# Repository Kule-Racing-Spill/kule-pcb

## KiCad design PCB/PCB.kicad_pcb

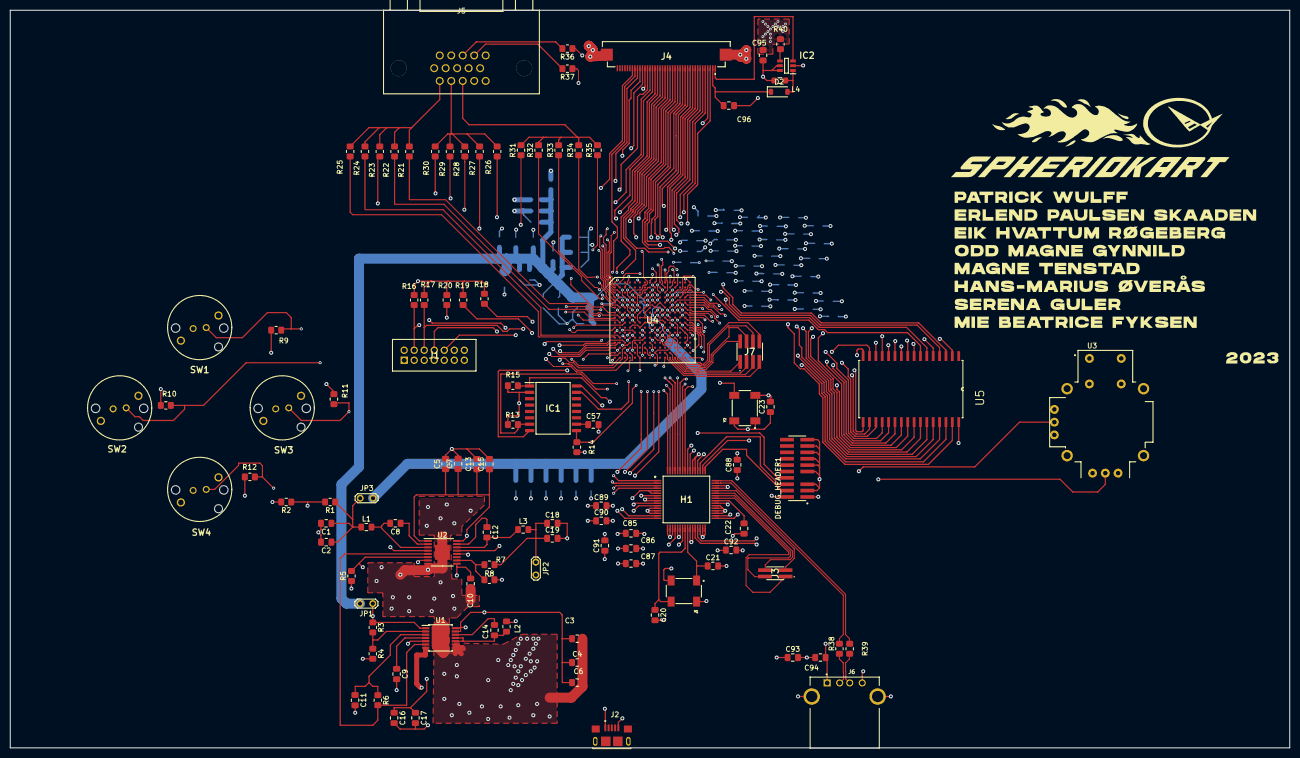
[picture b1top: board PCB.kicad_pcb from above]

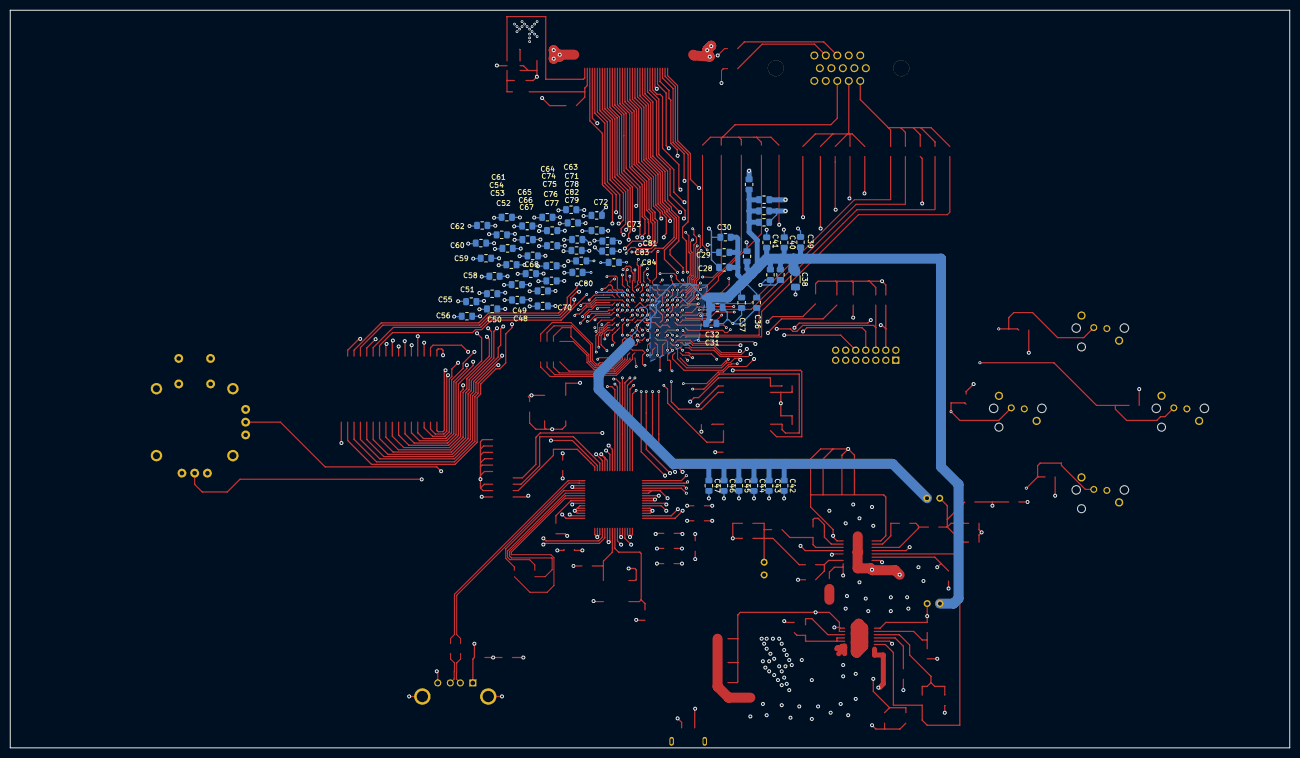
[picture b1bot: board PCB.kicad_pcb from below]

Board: 6 copper layers, 255.0 x 147.0 mm, 166 parts (60 on the bottom side), 163 nets.

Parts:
C1, C2, C16, C17, C18, C19: 22u; C_0805_2012Metric_Pad1.18x1.45mm_HandSolder
C3, C41, C94: 100u; C_0805_2012Metric_Pad1.18x1.45mm_HandSolder
C4, C5, C13, C92: 10u; C_0805_2012Metric_Pad1.18x1.45mm_HandSolder
C6, C7, C8, C12, C14, C15, C23, C57, C85, C86, C87, C88, C89, C90, C91: 100n; C_0805_2012Metric_Pad1.18x1.45mm_HandSolder
C9: 3.3n; C_0805_2012Metric_Pad1.18x1.45mm_HandSolder
C10, C11, C22, C93, C96: 1u; C_0805_2012Metric_Pad1.18x1.45mm_HandSolder
C20, C21: 12p; C_0805_2012Metric_Pad1.18x1.45mm_HandSolder
C24, C25, C26, C27, C28, C29, C30, C31, C39, C40, C42, C43, C44, C48, C49, C50, C51, C55, C56, C58, C59, C63, C64, C65, C66, C70, C71, C72, C73, C77, C78, C79, C80: 470n; C_0805_2012Metric_Pad1.18x1.45mm_HandSolder
C32, C33, C34, C35, C36, C37, C45, C46, C52, C53, C60, C61, C67, C68, C74, C75, C81, C82, C95: 4.7u; C_0805_2012Metric_Pad1.18x1.45mm_HandSolder
C38: 330u; C_1206_3216Metric_Pad1.33x1.80mm_HandSolder
C47, C54, C62, C69, C76, C83, C84: 47u; C_0805_2012Metric_Pad1.18x1.45mm_HandSolder
D2: MBR0520; D_SOD-123
DEBUG_HEADER1: FTSH-110-01-L-DV-007; SAMTEC_FTSH-110-01-L-DV-007
H1: EFM32GG332F1024-QFP64; QFP50P1200X1200X120-64N
IC1: S25FL256LAGMFI003; SOIC127P1030X265-16N
IC2: LT1932ES6#TRMPBF; SOT95P280X100-6N
J1: 0878311420
J2: USB_B_Micro; AMPHENOL_10118193-0001LF
J3: FTS-102-02-F-DV-TR; FTS-102-YY-XX-DV-TR
J4: 62684-402100ALF; 62684402100ALF
J5: L77HDE15SD1CH4FVGA; CONN_L77HDE15SD1CH4FVGA_AMP
J6: USB1130-15-A_REVA; GCT_USB1130-15-A_REVA
J7: FTSH-104-01-F-DV; FTSH-104-XX-YYY-DV
JP1, JP2, JP3: Jumper_2_Bridged; TestPoint_2Pads_Pitch2.54mm_Drill0.8mm
L1, L2: 1.5u; L_0805_2012Metric_Pad1.15x1.40mm_HandSolder
L3: 2.2u; L_0805_2012Metric_Pad1.15x1.40mm_HandSolder
L4: 6.8u; L_0805_2012Metric_Pad1.05x1.20mm_HandSolder
R1: 30.1k; R_0805_2012Metric_Pad1.20x1.40mm_HandSolder
R2, R4, R8: 22.1k; R_0805_2012Metric_Pad1.20x1.40mm_HandSolder
R3: 6.81k; R_0805_2012Metric_Pad1.20x1.40mm_HandSolder
R5, R6: 100k; R_0805_2012Metric_Pad1.20x1.40mm_HandSolder
R7: 73.2k; R_0805_2012Metric_Pad1.20x1.40mm_HandSolder
R9, R10, R11, R12, R16, R17: 10k; R_0805_2012Metric_Pad1.20x1.40mm_HandSolder
R13: 2.4k; R_0805_2012Metric_Pad1.20x1.40mm_HandSolder
R14, R15, R18, R19: 4.7k; R_0805_2012Metric_Pad1.20x1.40mm_HandSolder
R20: 330; R_0805_2012Metric_Pad1.20x1.40mm_HandSolder
R21, R26, R31, R40: 562; R_0805_2012Metric_Pad1.20x1.40mm_HandSolder
R22, R27, R32: 1124; R_0805_2012Metric_Pad1.20x1.40mm_HandSolder
R23, R28, R33: 2247; R_0805_2012Metric_Pad1.20x1.40mm_HandSolder
R24, R29, R34: 4495; R_0805_2012Metric_Pad1.20x1.40mm_HandSolder
R25, R30, R35: 8989; R_0805_2012Metric_Pad1.20x1.40mm_HandSolder
R36, R37: 100; R_0805_2012Metric_Pad1.20x1.40mm_HandSolder
R38, R39: 15; R_0805_2012Metric_Pad1.20x1.40mm_HandSolder
SW1, SW2, SW3, SW4: SW_Push; K12PBK15N
U1: TPS54325; TSSOP-14-1EP_4.4x5mm_P0.65mm
U2: TPS54294; HTSSOP-16-1EP_4.4x5mm_P0.65mm_EP3x3mm
U3: COM-09032; XDCR_COM-09032
U4: XC7A100T-FTG256; BGA256C100P16X16_1700X1700X155
U5: IS62C1024AL-35QLI-TR; SOIC127P1412X305-32N
Y1: Crystal_GND24; OSC_ECS-3953M-400-BN-TR
Y2: ECS-3953M-400-BN-TR; OSC_ECS-3953M-400-BN-TR

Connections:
+1V0: C24.1, C25.1, C26.1, C27.1, C28.1, C29.1, C30.1, C31.1, C32.1, C33.1, C34.1, C35.1, C36.1, C37.1, C38.1, C39.1, C40.1, C41.1, JP1.2 (B), U4.E10 (VCCBRAM), U4.F7 (VCCINT), U4.F9 (VCCINT), U4.F11 (VCCBRAM), U4.G6 (VCCINT), U4.H9 (VCCINT), U4.J6 (VCCINT), U4.K9 (VCCINT), U4.L8 (VCCINT)
+1V8: C42.1, C43.1, C44.1, C45.1, C46.1, C47.1, JP3.2 (B), U4.G8 (VCCADC_0), U4.G10 (VCCAUX), U4.J10 (VCCAUX), U4.K11 (VCCAUX), U4.L10 (VCCAUX)
+3.3V: C23.1, C48.1, C49.1, C50.1, C51.1, C52.1, C53.1, C54.1, C55.1, C56.1, C57.2, C58.1, C59.1, C60.1, C61.1, C62.1, C63.1, C64.1, C65.1, C66.1, C67.1, C68.1, C69.1, C70.1, C71.1, C72.1, C73.1, C74.1, C75.1, C76.1, C77.1, C78.1, C79.1, C80.1, C81.1, C82.1, C83.1, C84.1, C85.1, C86.1, C87.1, C88.1, C89.1, C90.1, C91.1, C92.1, C93.1, C95.1, DEBUG_HEADER1.01 (VCC), H1.7 (IOVDD_0), H1.23 (AVDD_1), H1.26 (IOVDD_3), H1.27 (AVDD_0), H1.39 (VDD_DREG), H1.45 (USB_VREGI), H1.46 (USB_VREGO), H1.55 (IOVDD_5), IC1.2 (VCC), IC2.5 (~SHDN), IC2.6 (VIN), J1.2, J4.4, JP2.2 (B), L4.1, R13.1, R14.2, R15.1, R16.1, R17.2, R18.2, R19.2, R20.1, SW1.1, SW2.1, SW3.1, SW4.1, U3.H1 (H+), U3.V1 (V+), U4.A6 (VCCO_35), U4.A16 (VCCO_15), U4.B3 (VCCO_35), U4.B13 (VCCO_15), U4.C10 (VCCO_15), U4.D7 (VCCO_35), U4.E4 (VCCO_35), U4.E7 (CFGBVS_0), U4.E14 (VCCO_15), U4.F1 (VCCO_35), U4.H15 (VCCO_15), U4.J2 (VCCO_35), U4.J12 (VCCO_15), U4.L6 (VCCO_0), U4.L16 (VCCO_14), U4.M3 (VCCO_34), U4.M9 (M0_0), U4.M13 (VCCO_14), U4.N10 (VCCO_14), U4.P7 (VCCO_14), U4.R4 (VCCO_34), U4.R14 (VCCO_14), U4.T1 (VCCO_34), U4.T11 (VCCO_14), U5.32 (VDD), Y2.1 (TRI-STATE), Y2.4 (VCC)
/FPGA/BLUE0: R31.1, U4.P3 (IO_L5N_T0_34)
/FPGA/BLUE1: R32.1, U4.M5 (IO_L6P_T0_34)
/FPGA/BLUE2: R33.1, U4.N4 (IO_L6N_T0_VREF_34)
/FPGA/BLUE3: R34.1, U4.R2 (IO_L7P_T1_34)
/FPGA/BLUE4: R35.1, U4.R1 (IO_L7N_T1_34)
/FPGA/CLK: H1.15 (PB7), U4.D10 (IO_0_15)
/FPGA/CS: H1.16 (PB8), U4.C8 (IO_L1P_T0_AD0P_15)
/FPGA/GPIO0: H1.64 (PE15), U4.A9 (IO_L2N_T0_AD8N_15)
/FPGA/GPIO1: H1.63 (PE14), U4.B9 (IO_L3P_T0_DQS_AD1P_15)
/FPGA/GPIO2: H1.62 (PE13), U4.A10 (IO_L3N_T0_DQS_AD1N_15)
/FPGA/GPIO3: H1.61 (PE12), U4.B10 (IO_L4P_T0_15)
/FPGA/GPIO4: H1.60 (PE11), U4.B11 (IO_L4N_T0_15)
/FPGA/GPIO5: H1.59 (PE10), U4.B12 (IO_L5P_T0_AD9P_15)
/FPGA/GPIO6: H1.58 (PE9), U4.A12 (IO_L5N_T0_AD9N_15)
/FPGA/GPIO7: H1.57 (PE8), U4.D8 (IO_L6P_T0_15)
/FPGA/GREEN0: R26.1, U4.N3 (IO_L3P_T0_DQS_34)
/FPGA/GREEN1: R27.1, U4.N2 (IO_L3N_T0_DQS_34)
/FPGA/GREEN2: R28.1, U4.N1 (IO_L4P_T0_34)
/FPGA/GREEN3: R29.1, U4.P1 (IO_L4N_T0_34)
/FPGA/GREEN4: R30.1, U4.P4 (IO_L5P_T0_34)
/FPGA/HSYNC: R36.1, U4.T2 (IO_L8N_T1_34)
/FPGA/MISO: H1.10 (PC1), U4.C9 (IO_L1N_T0_AD0N_15)
/FPGA/MOSI: H1.11 (PC2), U4.A8 (IO_L2P_T0_AD8P_15)
/FPGA/RED0: R21.1, U4.L5 (IO_0_34)
/FPGA/RED1: R22.1, U4.L4 (IO_L1P_T0_34)
/FPGA/RED2: R23.1, U4.M4 (IO_L1N_T0_34)
/FPGA/RED3: R24.1, U4.M2 (IO_L2P_T0_34)
/FPGA/RED4: R25.1, U4.M1 (IO_L2N_T0_34)
/FPGA/VSYNC: R37.1, U4.R3 (IO_L8P_T1_34)
/FPGA/done: H1.34 (PD6), R20.2, U4.H10 (DONE_0)
/FPGA/program_b: H1.33 (PD5), R19.1, U4.L9 (PROGRAM_B_0)
/microcontroller_unit/5V_IN: C3.1, C4.1, C5.1, C6.1, C7.1, C13.1, C15.1, C94.1, H1.52 (USB_VBUS), J2.1 (VBUS), J6.1 (VCC), U1.7 (EN), U1.13 (VIN), U1.14 (VCC), U2.1 (VIN1), U2.16 (VIN2)
/microcontroller_unit/D1+: J6.3 (D+), R39.2
/microcontroller_unit/D1-: J6.2 (D-), R38.2
/microcontroller_unit/D+: H1.48 (PF11), R39.1
/microcontroller_unit/D-: H1.47 (PF10), R38.1
GND: C1.2, C2.2, C3.2, C4.2, C5.2, C6.2, C7.2, C9.2, C10.2, C11.2, C13.2, C15.2, C16.2, C17.2, C18.2, C19.2, C20.2, C21.2, C22.2, C23.2, C24.2, C25.2, C26.2, C27.2, C28.2, C29.2, C30.2, C31.2, C32.2, C33.2, C34.2, C35.2, C36.2, C37.2, C38.2, C39.2, C40.2, C41.2, C42.2, C43.2, C44.2, C45.2, C46.2, C47.2, C48.2, C49.2, C50.2, C51.2, C52.2, C53.2, C54.2, C55.2, C56.2, C58.2, C59.2, C60.2, C61.2, C62.2, C63.2, C64.2, C65.2, C66.2, C67.2, C68.2, C69.2, C70.2, C71.2, C72.2, C73.2, C74.2, C75.2, C76.2, C77.2, C78.2, C79.2, C80.2, C81.2, C82.2, C83.2, C84.2, C85.2, C86.2, C87.2, C88.2, C89.2, C90.2, C91.2, C92.2, C93.2, C94.2, C95.2, C96.2, DEBUG_HEADER1.03 (GND), DEBUG_HEADER1.05 (GND), DEBUG_HEADER1.09 (GNDDetect), DEBUG_HEADER1.11 (GND), DEBUG_HEADER1.13 (GND), DEBUG_HEADER1.15 (GND), DEBUG_HEADER1.17 (GND), DEBUG_HEADER1.19 (GND), H1.5 (PA4), H1.6 (PA5), H1.8 (VSS_1), H1.9 (PC0), H1.12 (PC3), H1.13 (PC4), H1.14 (PC5), H1.17 (PA8), H1.18 (PA9), H1.19 (PA10), H1.21 (PB11), H1.22 (VSS_2), H1.30 (PD2), H1.31 (PD3), H1.32 (PD4), H1.35 (PD7), H1.36 (PD8), H1.37 (PC6), H1.38 (PC7), H1.53 (PF12), H1.54 (PF5), H1.56 (VSS_3), IC2.2 (GND), J1.1, J1.3, J1.5, J1.7, J1.9, J1.11, J1.13, J2.5 (GND), J4.29, J4.MH1, J4.MH2, J5.5, J5.6, J5.7, J5.8, J5.10, J6.4 (GND), J6.S1 (SHIELD), J6.S2 (SHIELD), R2.2, R4.2, R8.2, R9.1, R10.1, R11.1, R12.1, R40.2, U1.5 (GND), U1.8 (PGND1), U1.9 (PGND2), U1.15 (PwPd), U2.4 (PGND1), U2.8 (GND), U2.13 (PGND2), U2.17 (PwPd), U3.H3 (H-), U3.S1 (SHIELD), U3.S2 (SHIELD), U3.S3 (SHIELD), U3.S4 (SHIELD), U3.V3 (V-), U4.A1 (GND), U4.A11 (GND), U4.B8 (GND), U4.C5 (GND), U4.C15 (GND), U4.D2 (GND), U4.D12 (GND), U4.E9 (GND), U4.F6 (GND), U4.F8 (VCCBATT_0), U4.F10 (GND), U4.F16 (GND), U4.G3 (GND), U4.G7 (GNDADC_0), U4.G9 (GND), U4.G13 (GND), U4.H6 (GND), U4.H7 (VREFN_0), U4.H8 (VP_0), U4.J7 (VN_0), U4.J8 (VREFP_0), U4.J9 (GND), U4.J11 (GND), U4.K4 (GND), U4.K6 (GND), U4.K14 (GND), U4.L1 (GND), U4.L11 (GND), U4.L15 (IO_L3P_T0_DQS_PUDC_B_14), U4.M8 (GND), U4.M10 (M1_0), U4.M11 (M2_0), U4.N5 (GND), U4.N15 (GND), U4.P2 (GND), U4.P12 (GND), U4.R9 (GND), U4.T6 (GND), U4.T16 (GND), U5.16 (GND), Y1.2, Y1.4, Y2.2 (GND)
unnamed: D2.2 (A), IC2.1 (SW), L4.2
unnamed: C96.1, D2.1 (K), J4.2
unnamed: DEBUG_HEADER1.04 (SWDCLK), H1.49 (PF0)
unnamed: DEBUG_HEADER1.02 (SWDIO), H1.50 (PF1)
unnamed: DEBUG_HEADER1.06 (SWO), H1.51 (PF2)
unnamed: DEBUG_HEADER1.08 (nRESET), H1.20 (RESETN)
unnamed: C22.1, H1.40 (DECOUPLE)
unnamed: H1.1 (PA0), R9.2, SW1.2
unnamed: H1.2 (PA1), R10.2, SW2.2
unnamed: H1.3 (PA2), R11.2, SW3.2
unnamed: H1.4 (PA3), R12.2, SW4.2
unnamed: C20.1, H1.24 (PB13), Y1.3
unnamed: C21.1, H1.25 (PB14), Y1.1
unnamed: H1.41 (PC8), J3.1
unnamed: H1.42 (PC9), J3.2
unnamed: H1.43 (PC10), J3.4
unnamed: H1.44 (PC11), J3.3
unnamed: H1.28 (PD0), U3.H2 (H)
unnamed: H1.29 (PD1), U3.V2 (V)
unnamed: IC1.7 (CS#), R13.2, U4.L12 (IO_L6P_T0_FCS_B_14)
unnamed: IC1.1 (IO3_/_RESET#), R15.2, U4.K16 (IO_L2N_T0_D03_14)
unnamed: IC1.16 (SCK), U4.E8 (CCLK_0)
unnamed: IC1.15 (SI_/_IO0), U4.J13 (IO_L1P_T0_D00_MOSI_14)
unnamed: IC1.8 (SO_/_IO1), U4.J14 (IO_L1N_T0_D01_DIN_14)
unnamed: C57.1, IC1.10 (VSS)
unnamed: IC1.9 (WP#_/_IO2), R14.1, U4.K15 (IO_L2P_T0_D02_14)
unnamed: IC2.3 (LED), J4.1
unnamed: IC2.4 (RSET), R40.1
unnamed: J5.1, R21.2, R22.2, R23.2, R24.2, R25.2
unnamed: J5.2, R26.2, R27.2, R28.2, R29.2, R30.2
unnamed: J5.3, R31.2, R32.2, R33.2, R34.2, R35.2
unnamed: J5.13, R36.2
unnamed: J5.14, R37.2
unnamed: C16.1, C17.1, JP1.1 (A), L2.2, R3.1, U1.1 (VO)
unnamed: C18.1, C19.1, JP2.1 (A), L3.2, R7.1
unnamed: C1.1, C2.1, JP3.1 (A), L1.1, R1.1
unnamed: R6.2, U1.6 (PG), U2.5 (EN1)
unnamed: C9.1, U1.4 (SS)
unnamed: C14.2, L2.1, U1.10 (SW1), U1.11 (SW2)
unnamed: C14.1, U1.12 (VBST)
unnamed: R3.2, R4.1, U1.2 (VFB)
unnamed: C11.1, R6.1, U1.3 (VREG5)
unnamed: R5.2, U2.6 (PG1), U2.12 (EN2)
unnamed: C8.2, L1.2, U2.3 (SW1)
unnamed: C12.2, L3.1, U2.14 (SW2)
unnamed: C8.1, U2.2 (VBST1)
unnamed: C12.1, U2.15 (VBST2)
unnamed: R1.2, R2.1, U2.7 (VFB1)
unnamed: R7.2, R8.1, U2.10 (VFB2)
unnamed: C10.1, R5.1, U2.9 (VREG5)
unnamed: U4.G11 (IO_25_15), U5.21 (I/O7)
unnamed: J7.6, U4.R15 (IO_L9P_T1_DQS_14)
unnamed: J7.8, U4.T15 (IO_L10N_T1_D15_14)
unnamed: J7.4, U4.T14 (IO_L10P_T1_D14_14)
unnamed: U4.C12 (IO_L11N_T1_SRCC_15), U5.31 (A15)
unnamed: U4.C11 (IO_L11P_T1_SRCC_15), U5.2 (A16)
unnamed: U4.C13 (IO_L12N_T1_MRCC_15), U5.3 (A14)
unnamed: U4.D13 (IO_L12P_T1_MRCC_15), U5.28 (A13)
unnamed: U4.E13 (IO_L13N_T2_MRCC_15), U5.25 (A11)
unnamed: U4.N11 (IO_L13P_T2_MRCC_14), Y2.3 (OUTPUT)
unnamed: U4.E12 (IO_L13P_T2_MRCC_15), U5.4 (A12)
unnamed: U4.D11 (IO_L14N_T2_SRCC_15), U5.26 (A9)
unnamed: U4.E11 (IO_L14P_T2_SRCC_15), U5.23 (A10)
unnamed: U4.D15 (IO_L15N_T2_DQS_ADV_B_15), U5.5 (A7)
unnamed: J7.5, U4.T12 (IO_L15N_T2_DQS_DOUT_CSO_B_14)
unnamed: U4.D14 (IO_L15P_T2_DQS_15), U5.27 (A8)
unnamed: J7.3, U4.R12 (IO_L15P_T2_DQS_RDWR_B_14)
unnamed: J7.1, U4.T13 (IO_L16N_T2_A15_D31_14)
unnamed: U4.F13 (IO_L16N_T2_A27_15), U5.7 (A5)
unnamed: U4.F12 (IO_L16P_T2_A28_15), U5.6 (A6)
unnamed: J7.2, U4.R13 (IO_L16P_T2_CSI_B_14)
unnamed: J7.7, U4.R11 (IO_L17N_T2_A13_D29_14)
unnamed: U4.D16 (IO_L17N_T2_A25_15), U5.9 (A3)
unnamed: U4.E16 (IO_L17P_T2_A26_15), U5.8 (A4)
unnamed: U4.E15 (IO_L18N_T2_A23_15), U5.11 (A1)
unnamed: U4.F15 (IO_L18P_T2_A24_15), U5.10 (A2)
unnamed: U4.G12 (IO_L19N_T3_A21_VREF_15), U5.29 (~WE)
unnamed: U4.H11 (IO_L19P_T3_A22_15), U5.12 (A0)
unnamed: U4.H13 (IO_L20N_T3_A19_15), U5.30 (CE2)
unnamed: U4.H12 (IO_L20P_T3_A20_15), U5.24 (~OE)
unnamed: U4.F14 (IO_L21N_T3_DQS_A18_15), U5.13 (I/O0)
unnamed: U4.G14 (IO_L21P_T3_DQS_15), U5.22 (~CE1)
unnamed: U4.G16 (IO_L22N_T3_A16_15), U5.15 (I/O2)
unnamed: U4.H16 (IO_L22P_T3_A17_15), U5.14 (I/O1)
unnamed: U4.J16 (IO_L23N_T3_FWE_B_15), U5.18 (I/O4)
unnamed: U4.J15 (IO_L23P_T3_FOE_B_15), U5.17 (I/O3)
unnamed: U4.G15 (IO_L24N_T3_RS0_15), U5.20 (I/O6)
unnamed: U4.H14 (IO_L24P_T3_RS1_15), U5.19 (I/O5)
unnamed: J4.3, U4.D5 (IO_L6N_T0_VREF_35)
unnamed: J4.5, U4.C2 (IO_L7N_T1_AD6N_35)
unnamed: J4.7, U4.A2 (IO_L8N_T1_AD14N_35)
unnamed: J4.6, U4.B2 (IO_L8P_T1_AD14P_35)
unnamed: J4.9, U4.B1 (IO_L9N_T1_DQS_AD7N_35)
unnamed: J4.8, U4.C1 (IO_L9P_T1_DQS_AD7P_35)
unnamed: J4.11, U4.D1 (IO_L10N_T1_AD15N_35)
unnamed: J4.10, U4.E2 (IO_L10P_T1_AD15P_35)
unnamed: J4.13, U4.D3 (IO_L11N_T1_SRCC_35)
unnamed: J4.12, U4.E3 (IO_L11P_T1_SRCC_35)
unnamed: J4.15, U4.C4 (IO_L12N_T1_MRCC_35)
unnamed: J4.14, U4.D4 (IO_L12P_T1_MRCC_35)
unnamed: J4.17, U4.E5 (IO_L13N_T2_MRCC_35)
unnamed: J4.16, U4.F5 (IO_L13P_T2_MRCC_35)
unnamed: J4.19, U4.F3 (IO_L14N_T2_SRCC_35)
unnamed: J4.18, U4.F4 (IO_L14P_T2_SRCC_35)
unnamed: J4.21, U4.E1 (IO_L15N_T2_DQS_35)
unnamed: J4.20, U4.F2 (IO_L15P_T2_DQS_35)
unnamed: J4.23, U4.G4 (IO_L16N_T2_35)
unnamed: J4.22, U4.G5 (IO_L16P_T2_35)
unnamed: J4.25, U4.G1 (IO_L17N_T2_35)
unnamed: J4.24, U4.G2 (IO_L17P_T2_35)
unnamed: J4.27, U4.H4 (IO_L18N_T2_35)
unnamed: J4.26, U4.H5 (IO_L18P_T2_35)
unnamed: J4.28, U4.J5 (IO_L19P_T3_35)
unnamed: J4.31, U4.H1 (IO_L20N_T3_35)
unnamed: J4.30, U4.H2 (IO_L20P_T3_35)
unnamed: J4.33, U4.H3 (IO_L21N_T3_DQS_35)
unnamed: J4.32, U4.J3 (IO_L21P_T3_DQS_35)
unnamed: J4.34, U4.K1 (IO_L22P_T3_35)
unnamed: R18.1, U4.K10 (INIT_B_0)
unnamed: J1.6, R17.1, U4.L7 (TCK_0)
unnamed: J1.10, U4.N7 (TDI_0)
unnamed: J1.8, U4.N8 (TDO_0)
unnamed: J1.4, R16.2, U4.M7 (TMS_0)

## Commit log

2023-09-05 Intial commit
2023-09-07 add library
2023-09-07 Add lib
2023-09-07 Power
2023-09-09 Finish sketch of power supply
2023-09-11 Add stuff
2023-09-12 Edited pins on components
2023-09-16 Sketch
2023-09-18 Fix wiring
2023-09-18 Set resistor values
2023-09-19 Backups
2023-09-25 pcb til mcu, mangler ground og powersupply
2023-09-26 Added FPGA
2023-09-26 Flash
2023-09-26 FPGA - Lagt til Flash
2023-09-26 Adding unit C and D to FPGA (Stil missing unit B)
2023-09-26 Debugg added, missing one unit still
2023-09-27 Work
2023-09-27 more work
2023-09-27 Some error fix
2023-09-27 Remaining resistor and capacitor values set
2023-09-27 pls work
2023-09-27 Footprints
2023-09-28 Start PCB
2023-09-28 more
2023-09-28 schematic fixes
2023-09-28 schematic fixes.2
2023-09-28 Work on PCB
2023-09-29 hello
2023-09-29 push<
2023-09-30 FPGA Done?
2023-09-30 Error handling and line management
2023-10-01 Finish PCB
2023-10-01 Small fixes
2023-10-03 logo+navn
2023-10-03 Edited clearance
2023-10-03 finished
2023-10-04 start fix routing
2023-10-04 Correct mistakes
